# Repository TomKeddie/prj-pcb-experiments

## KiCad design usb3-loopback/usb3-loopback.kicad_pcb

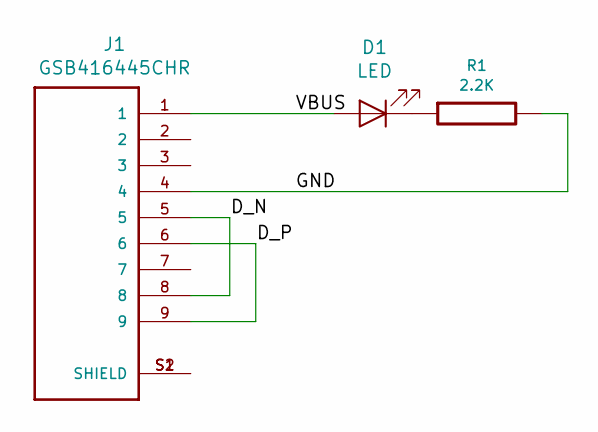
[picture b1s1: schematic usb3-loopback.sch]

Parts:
D1: LED; C_0805_2012Metric
J1: GSB416445CHR; AMPHENOL_GSB416445CHR
R1: 2.2K; R_0603_1608Metric

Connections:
/D_N: J1.5, J1.8
/D_P: J1.6, J1.9
/GND: J1.4, R1.2
/VBUS: D1.2 (A), J1.1
unnamed: D1.1 (K), R1.1
unnamed: J1.S1 (SHIELD), J1.S2 (SHIELD)

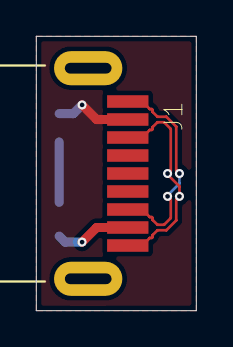
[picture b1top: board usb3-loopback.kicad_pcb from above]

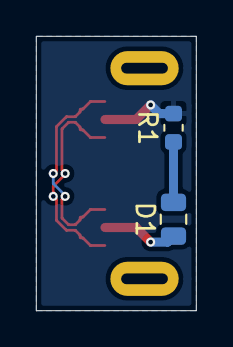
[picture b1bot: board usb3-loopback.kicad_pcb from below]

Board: 2 copper layers, 8.9 x 15.2 mm, 3 parts (2 on the bottom side), 6 nets.
